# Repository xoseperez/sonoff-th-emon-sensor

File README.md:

# Sonoff TH Energy Monitor Sensor

This repo includes Open Source Hardware (OSHW) to connect a CT to a Sonoff TH via the 2.5mm jack port. To do it we will use a I2C ADC board with a 3.5mm jack on one side to connect the CT and different connectors on the other to wire a TRRS cable.

This repository includes a board with a ADC121 single-channel ADC and a ADS1114 four channel ADC.

# License

The MIT License (MIT)

Copyright (C) 2016-2018 by Xose Pérez <xose dot perez at gmail dot com>

Permission is hereby granted, free of charge, to any person obtaining a copy
of this software and associated documentation files (the "Software"), to deal
in the Software without restriction, including without limitation the rights
to use, copy, modify, merge, publish, distribute, sublicense, and/or sell
copies of the Software, and to permit persons to whom the Software is
furnished to do so, subject to the following conditions:

The above copyright notice and this permission notice shall be included in all
copies or substantial portions of the Software.

THE SOFTWARE IS PROVIDED "AS IS", WITHOUT WARRANTY OF ANY KIND, EXPRESS OR
IMPLIED, INCLUDING BUT NOT LIMITED TO THE WARRANTIES OF MERCHANTABILITY,
FITNESS FOR A PARTICULAR PURPOSE AND NONINFRINGEMENT. IN NO EVENT SHALL THE
AUTHORS OR COPYRIGHT HOLDERS BE LIABLE FOR ANY CLAIM, DAMAGES OR OTHER
LIABILITY, WHETHER IN AN ACTION OF CONTRACT, TORT OR OTHERWISE, ARISING FROM,
OUT OF OR IN CONNECTION WITH THE SOFTWARE OR THE USE OR OTHER DEALINGS IN THE
SOFTWARE.

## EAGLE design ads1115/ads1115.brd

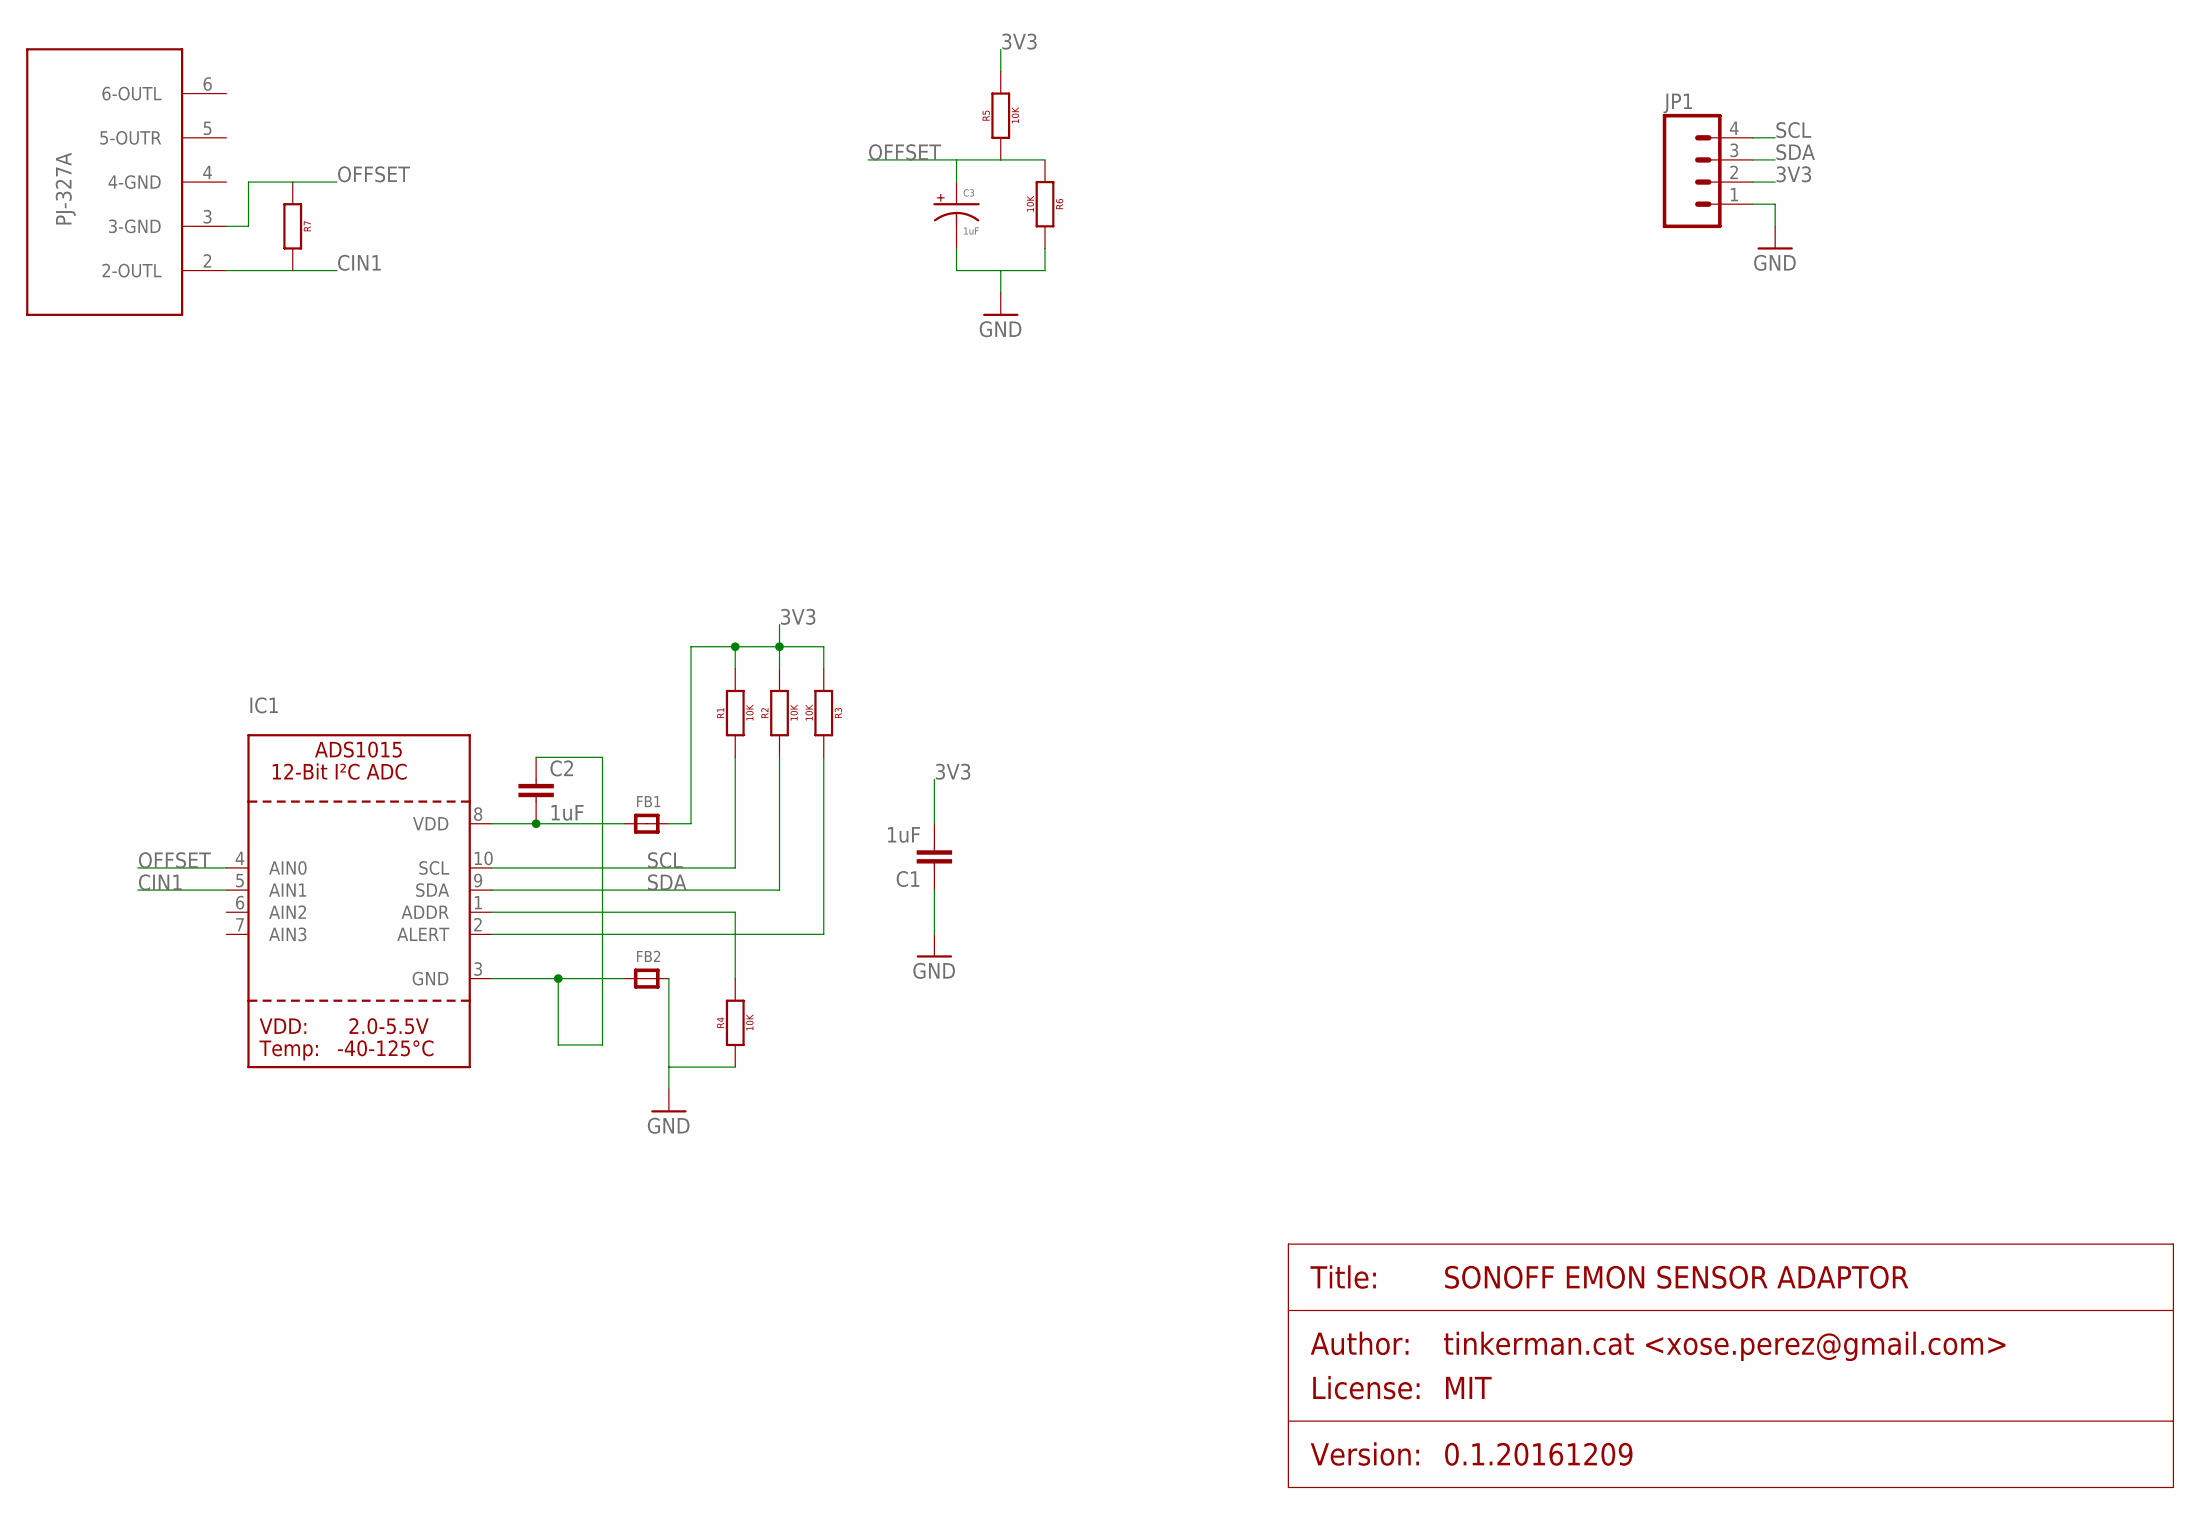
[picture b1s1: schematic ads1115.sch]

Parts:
C1, C2: 1uF; 0805
C3: 1uF; PANASONIC_C
CURR1: PJ-327A
FB1, FB2: FERRITE_0805MP; _0805MP
IC1: ADC_ADS1015; MSOP10
JP1: M04PTH; 1X04
R1, R2, R3, R4, R5, R6: 10K; 0805
R7: RESISTOR0805; 0805

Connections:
3V3: C1.2, FB1.2, JP1.2, R1.2, R2.2, R3.1, R5.2
CIN1: CURR1.2 (2-OUTL), IC1.5 (AIN1), R7.2
GND: C1.1, C3.-, FB2.2, JP1.1, R4.1, R6.2
unnamed: C2.2, FB1.1, IC1.8 (VDD)
unnamed: IC1.2 (ALERT), R3.2
unnamed: IC1.1 (ADDR), R4.2
unnamed: C2.1, FB2.1, IC1.3 (GND)
OFFSET: C3.+, CURR1.3 (3-GND), IC1.4 (AIN0), R5.1, R6.1, R7.1
SCL: IC1.10 (SCL), JP1.4, R1.1
SDA: IC1.9 (SDA), JP1.3, R2.1

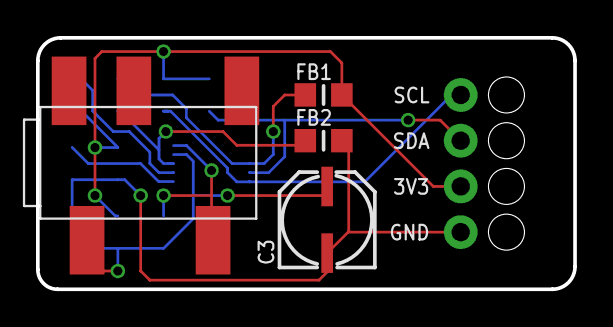
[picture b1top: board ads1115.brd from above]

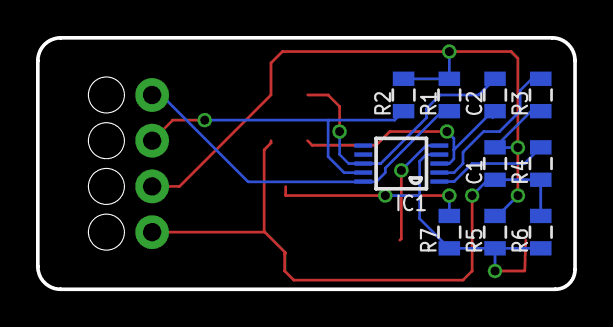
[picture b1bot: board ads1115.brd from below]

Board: 2 copper layers, 29.8 x 14.0 mm, 15 parts (10 on the bottom side), 10 nets.

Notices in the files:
ads1115/ads1115.sch:
PROJECT_LICENSE: MIT
parts and their libraries:
microbuilder: This work is placed in the public domain, and may be freely used for commercial and non-commercial work with the following conditions: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
SparkFun-Aesthetics: Licensing: Creative Commons ShareAlike 4.0 International - https://creativecommons.org/licenses/by-sa/4.0
